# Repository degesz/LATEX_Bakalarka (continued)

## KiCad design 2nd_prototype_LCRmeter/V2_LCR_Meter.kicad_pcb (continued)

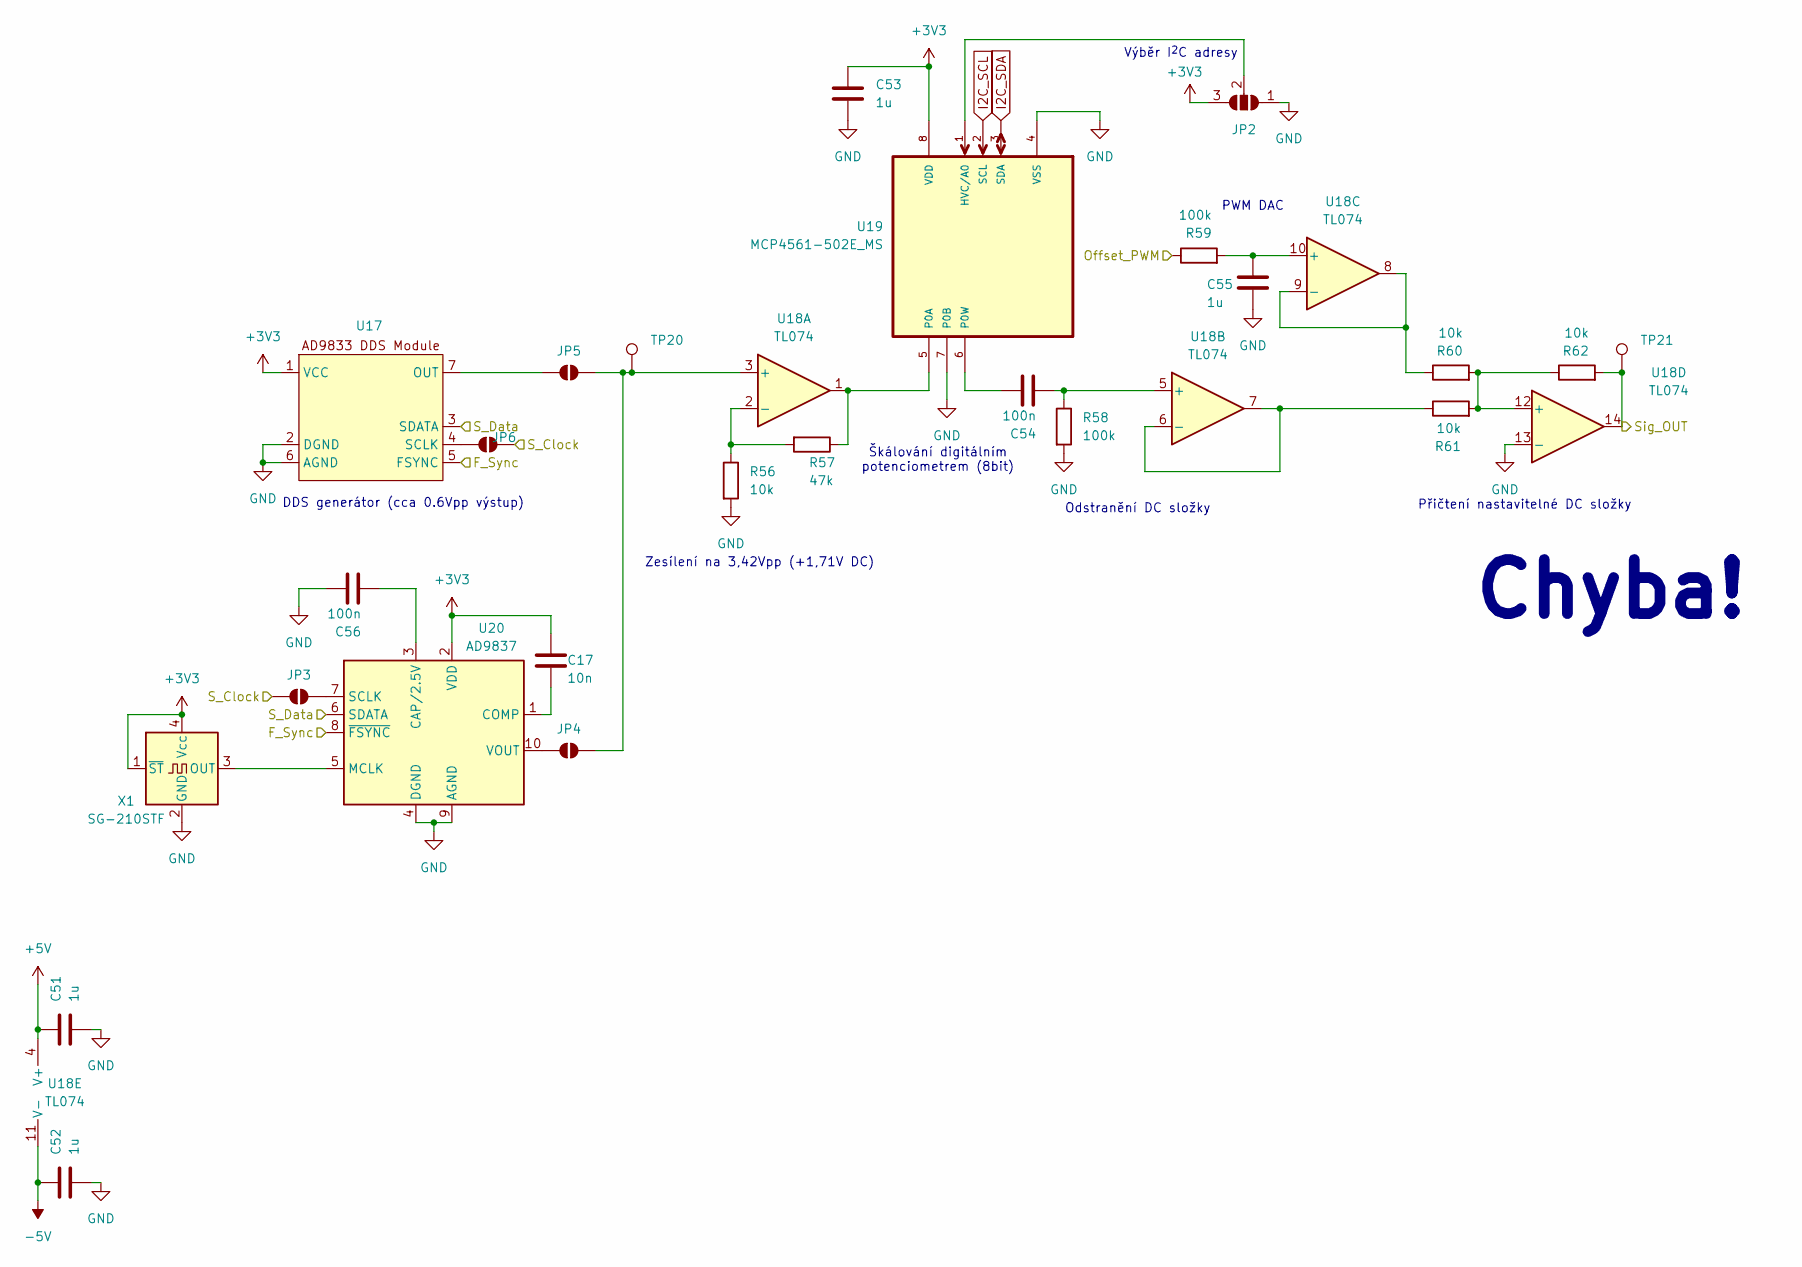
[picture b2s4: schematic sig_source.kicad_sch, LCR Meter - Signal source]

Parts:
C17: 10n; C_0603_1608Metric_Pad1.08x0.95mm_HandSolder
C51, C52, C53, C55: 1u; C_0603_1608Metric_Pad1.08x0.95mm_HandSolder
C54, C56: 100n; C_0603_1608Metric_Pad1.08x0.95mm_HandSolder
JP2: SolderJumper_3_Open; SolderJumper-3_P1.3mm_Open_RoundedPad1.0x1.5mm
JP3, JP4, JP5, JP6: SolderJumper_2_Open; SolderJumper-2_P1.3mm_Open_RoundedPad1.0x1.5mm
R56, R60, R61, R62: 10k; R_0603_1608Metric_Pad0.98x0.95mm_HandSolder
R57: 47k; R_0603_1608Metric_Pad0.98x0.95mm_HandSolder
R58, R59: 100k; R_0603_1608Metric_Pad0.98x0.95mm_HandSolder
TP20, TP21: TestPoint; Pin_D1.0mm_L10.0mm
U17: AD9833_Module
U18: TL074; TSSOP-14_4.4x5mm_P0.65mm
U19: MCP4561-502E_MS; MSOP-8_3x3mm_P0.65mm; MPN MCP4561-502E/MS
U20: AD9837; LFCSP-WD-10-1EP_3x3mm_P0.5mm_EP1.64x2.38mm
X1: SG-210STF; Oscillator_SMD_SeikoEpson_SG210-4Pin_2.5x2.0mm

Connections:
+3V3: C17.1, C53.2, JP2.3 (B), U17.1 (VCC), U19.8 (VDD), U20.2 (VDD), X1.1 (~ST), X1.4 (Vcc); also elsewhere on the board
+5V: C51.2, U18.4 (V+); also elsewhere on the board
-5V: C52.2, U18.11 (V-); also elsewhere on the board
/Analog frontend/Sig_IN: R62.2, TP21.1, U18.14; also elsewhere on the board
/Drive signal source/F_Sync: U17.5 (FSYNC), U20.8 (~FSYNC); also elsewhere on the board
/Drive signal source/Offset_PWM: R59.1; also elsewhere on the board
/Drive signal source/S_Clock: JP3.1 (A), JP6.2 (B); also elsewhere on the board
/Drive signal source/S_Data: U17.3 (SDATA), U20.6 (SDATA); also elsewhere on the board
GND: C51.1, C52.1, C53.1, C55.1, C56.2, JP2.1 (A), R56.2, R58.2, U17.2 (DGND), U17.6 (AGND), U18.13 (-), U19.4 (VSS), U19.7 (P0B), U20.4 (DGND), U20.9 (AGND), X1.2 (GND); also elsewhere on the board
I2C_SCL: U19.2 (SCL); also elsewhere on the board
I2C_SDA: U19.3 (SDA); also elsewhere on the board
unnamed: JP2.2 (C), U19.1 (HVC/A0)
unnamed: JP3.2 (B), U20.7 (SCLK)
unnamed: JP4.1 (A), U20.10 (VOUT)
unnamed: JP4.2 (B), JP5.2 (B), TP20.1, U18.3 (+)
unnamed: JP5.1 (A), U17.7 (OUT)
unnamed: JP6.1 (A), U17.4 (SCLK)
unnamed: R56.1, R57.2, U18.2 (-)
unnamed: C54.1, R58.1, U18.5 (+)
unnamed: R61.1, U18.6 (-), U18.7
unnamed: C55.2, R59.2, U18.10 (+)
unnamed: R60.1, U18.8, U18.9 (-)
unnamed: R60.2, R61.2, R62.1, U18.12 (+)
unnamed: R57.1, U18.1, U19.5 (P0A)
unnamed: C54.2, U19.6 (P0W)
unnamed: C56.1, U20.3 (CAP/2.5V)
unnamed: C17.2, U20.1 (COMP)
unnamed: U20.5 (MCLK), X1.3 (OUT)

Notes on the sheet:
Výběr I^{2}C adresy
Škálování digitálním potenciometrem (8bit)
Přičtení nastavitelné DC složky
Odstranění DC složky
Zesílení na 3,42Vpp (+1,71V DC)
DDS generátor (cca 0.6Vpp výstup)
Chyba!
PWM DAC

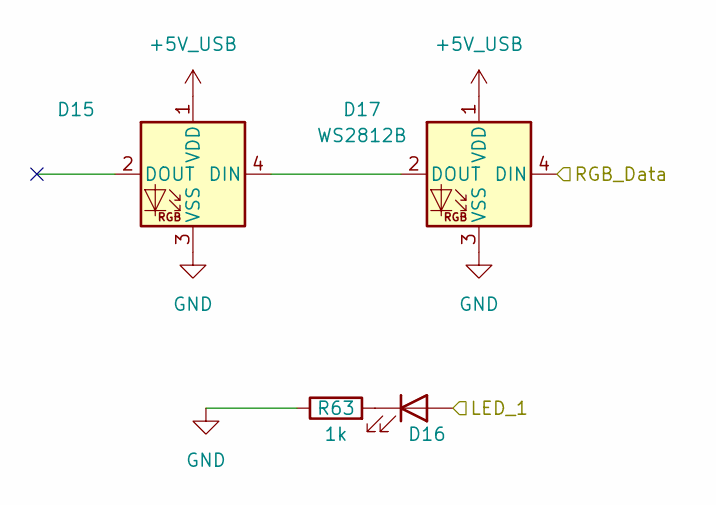
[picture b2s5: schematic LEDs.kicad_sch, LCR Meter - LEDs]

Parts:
D15, D17: WS2812B; LED_WS2812B_PLCC4_5.0x5.0mm_P3.2mm
D16: LED; LED_miniPLCC_2315
R63: 1k; R_0603_1608Metric_Pad0.98x0.95mm_HandSolder

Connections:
+5V_USB: D15.1 (VDD), D17.1 (VDD); also elsewhere on the board
/LEDs/LED_1: D16.2 (A); also elsewhere on the board
/LEDs/RGB_Data: D17.4 (DIN); also elsewhere on the board
GND: D15.3 (VSS), D17.3 (VSS), R63.1; also elsewhere on the board
unnamed: D15.4 (DIN), D17.2 (DOUT)
unnamed: D16.1 (K), R63.2

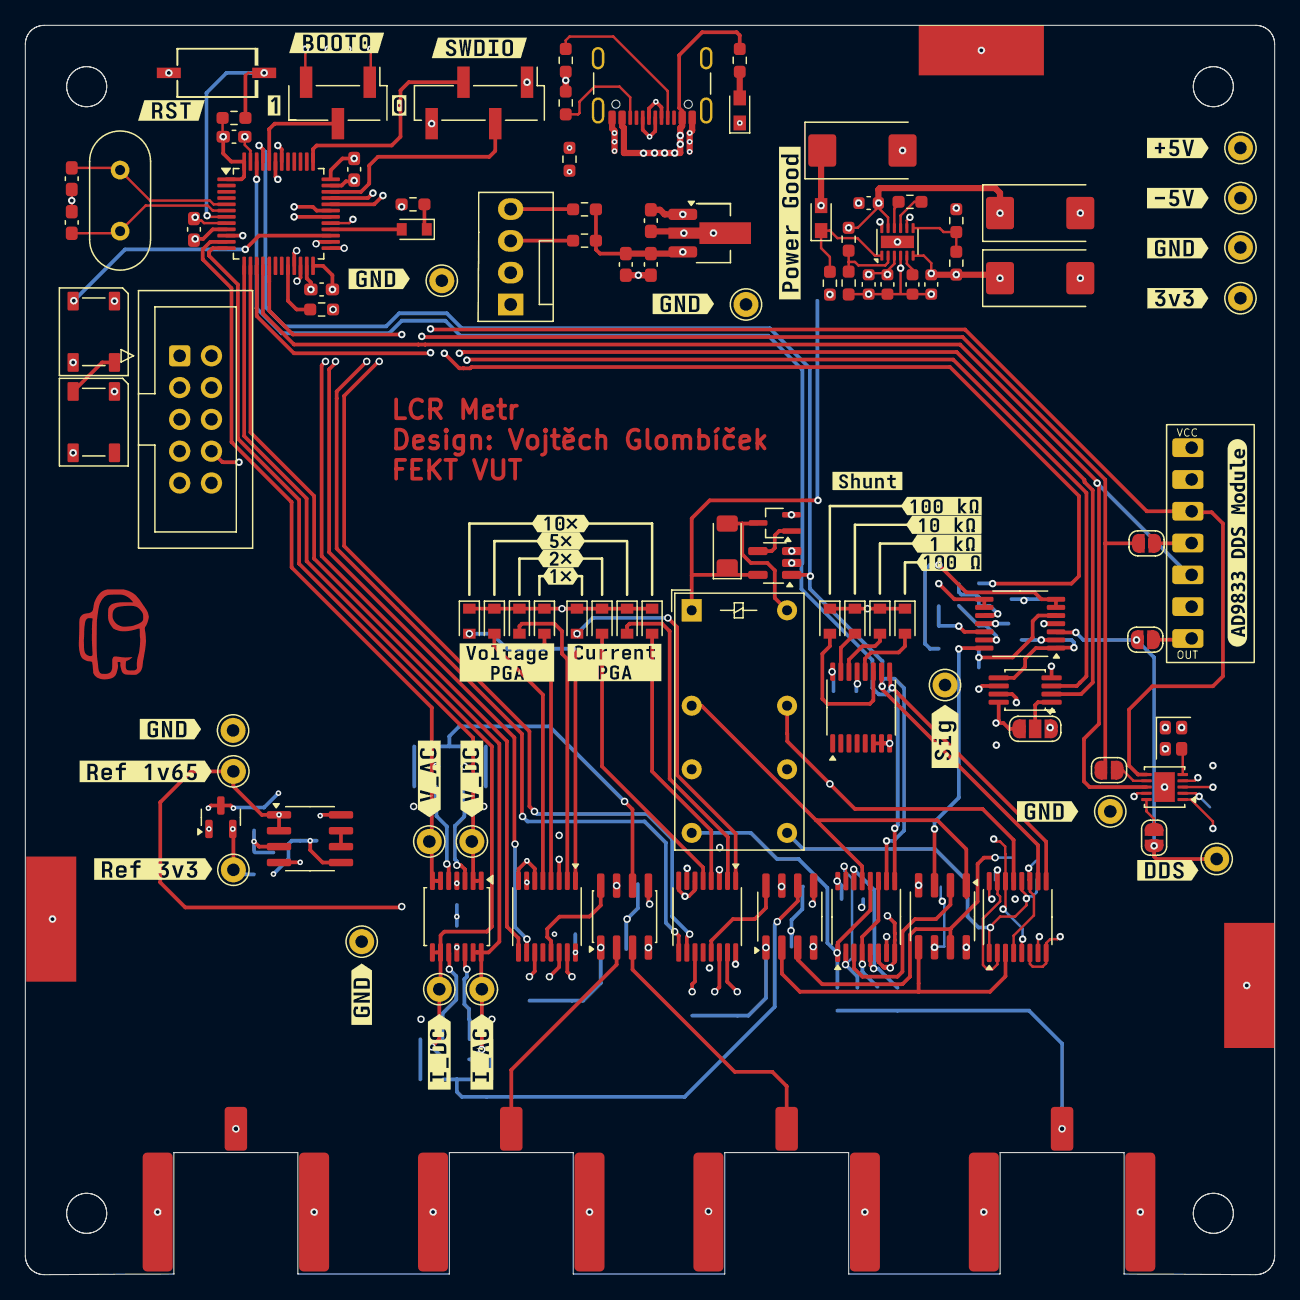
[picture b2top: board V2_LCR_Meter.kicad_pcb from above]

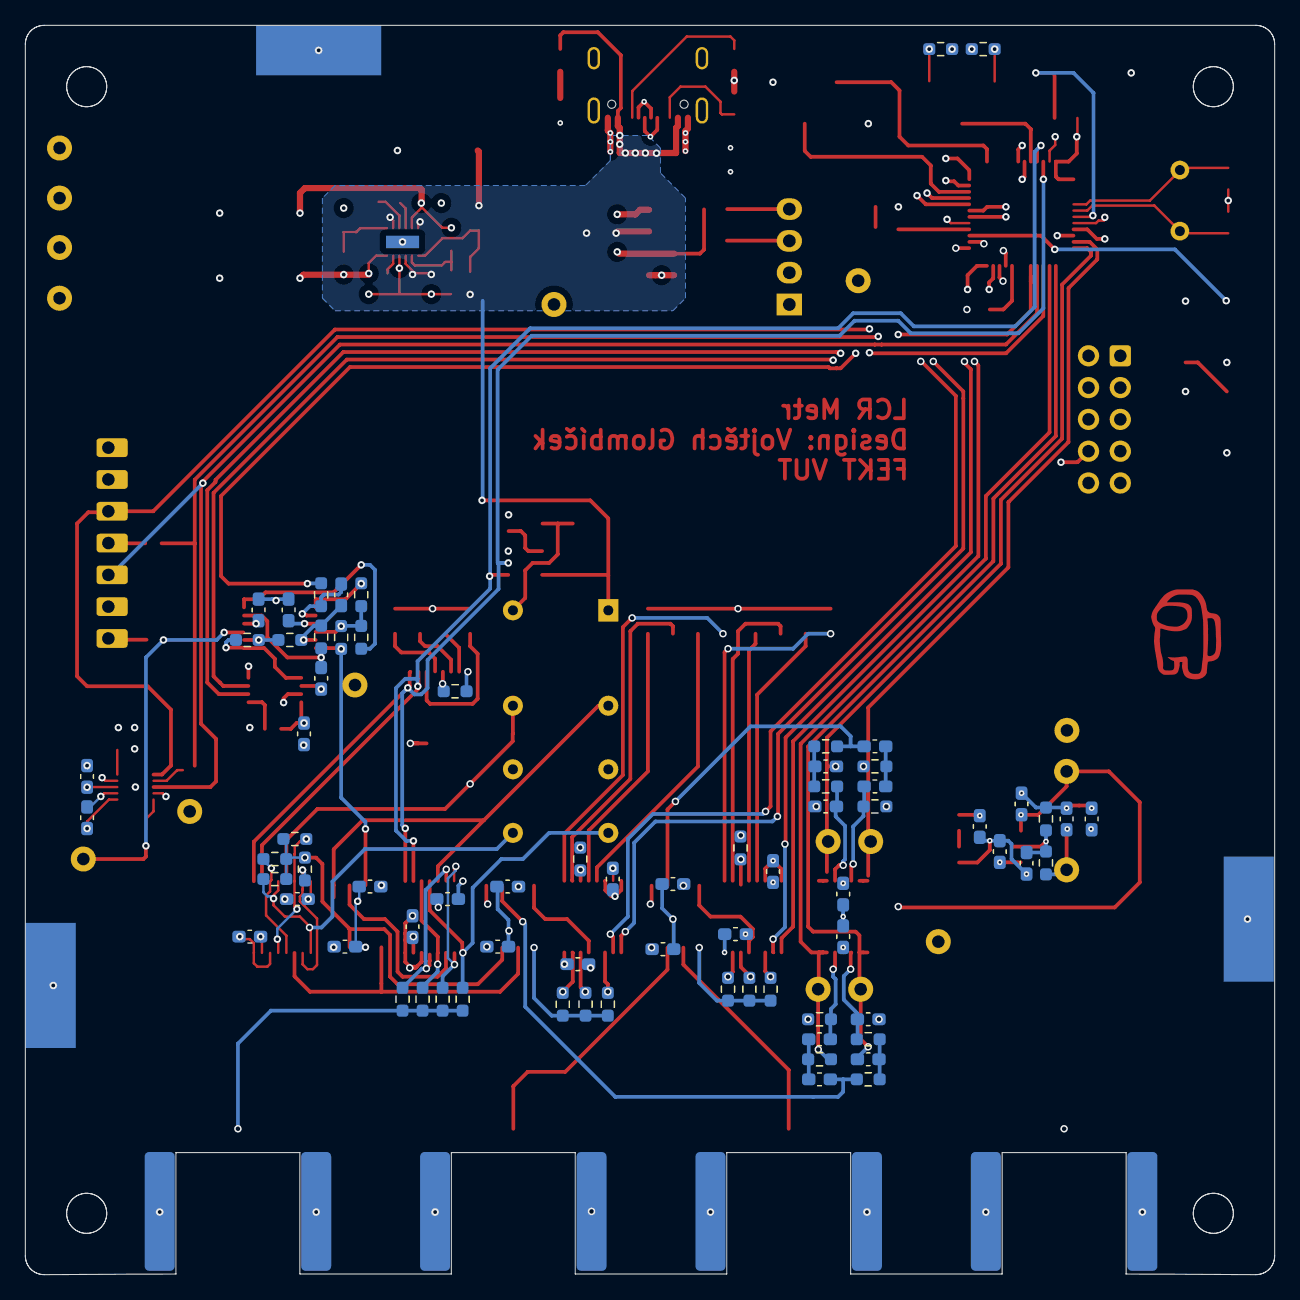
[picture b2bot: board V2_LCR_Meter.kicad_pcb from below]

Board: 6 copper layers, 99.8 x 99.8 mm, 212 parts (73 on the bottom side), 123 nets.

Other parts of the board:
kibuzzard-69A6FBA9: G***; kibuzzard-69A6FBA9
kibuzzard-69A6FBC7: G***; kibuzzard-69A6FBC7
kibuzzard-69A6FBD5: G***; kibuzzard-69A6FBD5
kibuzzard-69A6FBDC: G***; kibuzzard-69A6FBDC
kibuzzard-69A6FC6B: G***; kibuzzard-69A6FC6B
kibuzzard-69A6FC8C: G***; kibuzzard-69A6FC8C
kibuzzard-69A6FD3E: G***; kibuzzard-69A6FD3E
kibuzzard-69A6FD14: G***; kibuzzard-69A6FD14
kibuzzard-69A6FD47: G***; kibuzzard-69A6FD47
kibuzzard-69A6FD75: G***; kibuzzard-69A6FD75
kibuzzard-69A6FDE1: G***; kibuzzard-69A6FDE1
kibuzzard-69A0511F: G***; kibuzzard-69A0511F
kibuzzard-69A0516F: G***; kibuzzard-69A0516F
kibuzzard-69A0517C: G***; kibuzzard-69A0517C
kibuzzard-69B032D8: G***; kibuzzard-69B032D8
kibuzzard-69B032F6: G***; kibuzzard-69B032F6
kibuzzard-69B01019: G***; kibuzzard-69B01019
kibuzzard-69B01039: G***; kibuzzard-69B01039
kibuzzard-69B01057: G***; kibuzzard-69B01057
kibuzzard-69B03341: G***; kibuzzard-69B03341
kibuzzard-69B03368: G***; kibuzzard-69B03368
kibuzzard-69B03378: G***; kibuzzard-69B03378
kibuzzard-699D9FD2: G***; kibuzzard-699D9FD2
kibuzzard-699DA05C: G***; kibuzzard-699DA05C
kibuzzard-699DA06A, kibuzzard-699DA06A#2, kibuzzard-699DA06A#3, kibuzzard-699DA06A#4, kibuzzard-699DA06A#5, kibuzzard-699DA06A#6: G***; kibuzzard-699DA06A
kibuzzard-699DA06F: G***; kibuzzard-699DA06F
kibuzzard-699DA048: G***; kibuzzard-699DA048
kibuzzard-699DB946: G***; kibuzzard-699DB946
kibuzzard-699DC026: G***; kibuzzard-699DC026

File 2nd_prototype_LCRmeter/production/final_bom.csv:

Designator,Footprint,Quantity,Value,LCSC Part #
"C1, C2",0603,2,20p,
"C10, C14, C19, C20, C21, C22, C23, C24, C25, C26, C27, C3, C31, C35, C36, C37, C38, C39, C4, C40, C41, C42, C5, C51, C52, C53, C55, C6",0603,28,1u,
"C11, C12, C28, C32, C33, C34, C43, C44, C45, C46, C47, C48, C49, C50, C54, C56",0603,16,100n,
"C13, C15, C16, C8, C9",0603,5,4.7u,
C17,0603,1,10n,
"C18, C29, C7",CP_EIA-7343-30_AVX-N_HandSolder,3,470u,
"D1, D18",LED_miniPLCC_2315_Handsoldering,2,LED,
"D10, D11, D12, D13, D16, D2, D3, D4, D5, D6, D7, D8, D9",LED_miniPLCC_2315,13,LED,
D14,D_MiniMELF,1,D_Schottky,
"D15, D17",LED_WS2812B_PLCC4_5.0x5.0mm_P3.2mm,2,WS2812B,
J1,PinHeader_1x04_P2.54mm_Vertical_SMD_Pin1Left,1,ST-Link,
J2,FanPinHeader_1x04_P2.54mm_Vertical,1,Display OLED,
J3,IDC-Header_2x05_P2.54mm_Vertical,1,IDC 2x5,
J4,USB_C_Receptacle_GCT_USB4105-xx-A_16P_TopMnt_Horizontal,1,USB_C_Receptacle_USB2.0_16P,
"J6, J7, J8, J9",BNC_Gold,4,Conn_Coaxial,
K1,Relay_DPDT_Finder_30.22,1,Relay_DPDT,
Q1,SOT-323_SC-70_Handsoldering,1,NX3008NBK,
"R1, R22, R3, R35, R4, R54, R55, R56, R60, R61, R62, R64",0603,12,10k,
"R10, R11, R7",0603,3,1k5,
"R12, R2, R5, R9",0603,4,4k7,
"R13, R21, R34, R37, R38, R6, R63, R8",0603,8,1k,
"R14, R17, R18, R19, R23, R24, R36, R39, R41, R42, R43, R44, R45, R58, R59",0603,15,100k,
"R15, R40",0603,2,25k,
R16,0603,1,11k,
"R20, R33",0603,2,100R,
R57,0603,1,47k,
"R65, R66",0603,2,5k1,
SW1,SW-SMD_L6.1-W3.7-LS7.9,1,SW_SPST,
"TP1, TP10, TP11, TP12, TP13, TP14, TP15, TP16, TP17, TP18, TP19, TP2, TP20, TP21, TP5, TP6, TP7",Pin_D1.0mm_L10.0mm,17,TestPoint,
U1,LQFP-48_7x7mm_P0.5mm,1,STM32F103C8Tx,
U10,SOIC-8_3.9x4.9mm_P1.27mm,1,TL072,
"U11, U13, U14, U5, U8",TSSOP-16_4.4x5mm_P0.65mm,5,CD74HC4052,
"U12, U6",SOIC-8_3.9x4.9mm_P1.27mm,2,INA823,
U15,SOT-23,1,REF3033,
U16,SOT-23-5_HandSoldering,1,74LVC1G02,
U17,AD9833_Module,1,~,
"U18, U7",TSSOP-14_4.4x5mm_P0.65mm,2,TL074,
U19,MSOP-8_3x3mm_P0.65mm,1,MCP4561-502E_MS,MCP4561-502E/MS
U2,WSON-12-1EP_3x2mm_P0.5mm_EP1x2.65_ThermalVias,1,LM27762,
U20,LFCSP-WD-10-1EP_3x3mm_P0.5mm_EP1.64x2.38mm,1,AD9837,
U3,SOT-89-3_Handsoldering,1,HT75xx-1-SOT89,
U4,SOIC-8_3.9x4.9mm_P1.27mm,1,OPA2192,
X1,Oscillator_SMD_SeikoEpson_SG210-4Pin_2.5x2.0mm,1,SG-210STF,
Y1,Crystal_HC49-U_Vertical,1,8MHz,

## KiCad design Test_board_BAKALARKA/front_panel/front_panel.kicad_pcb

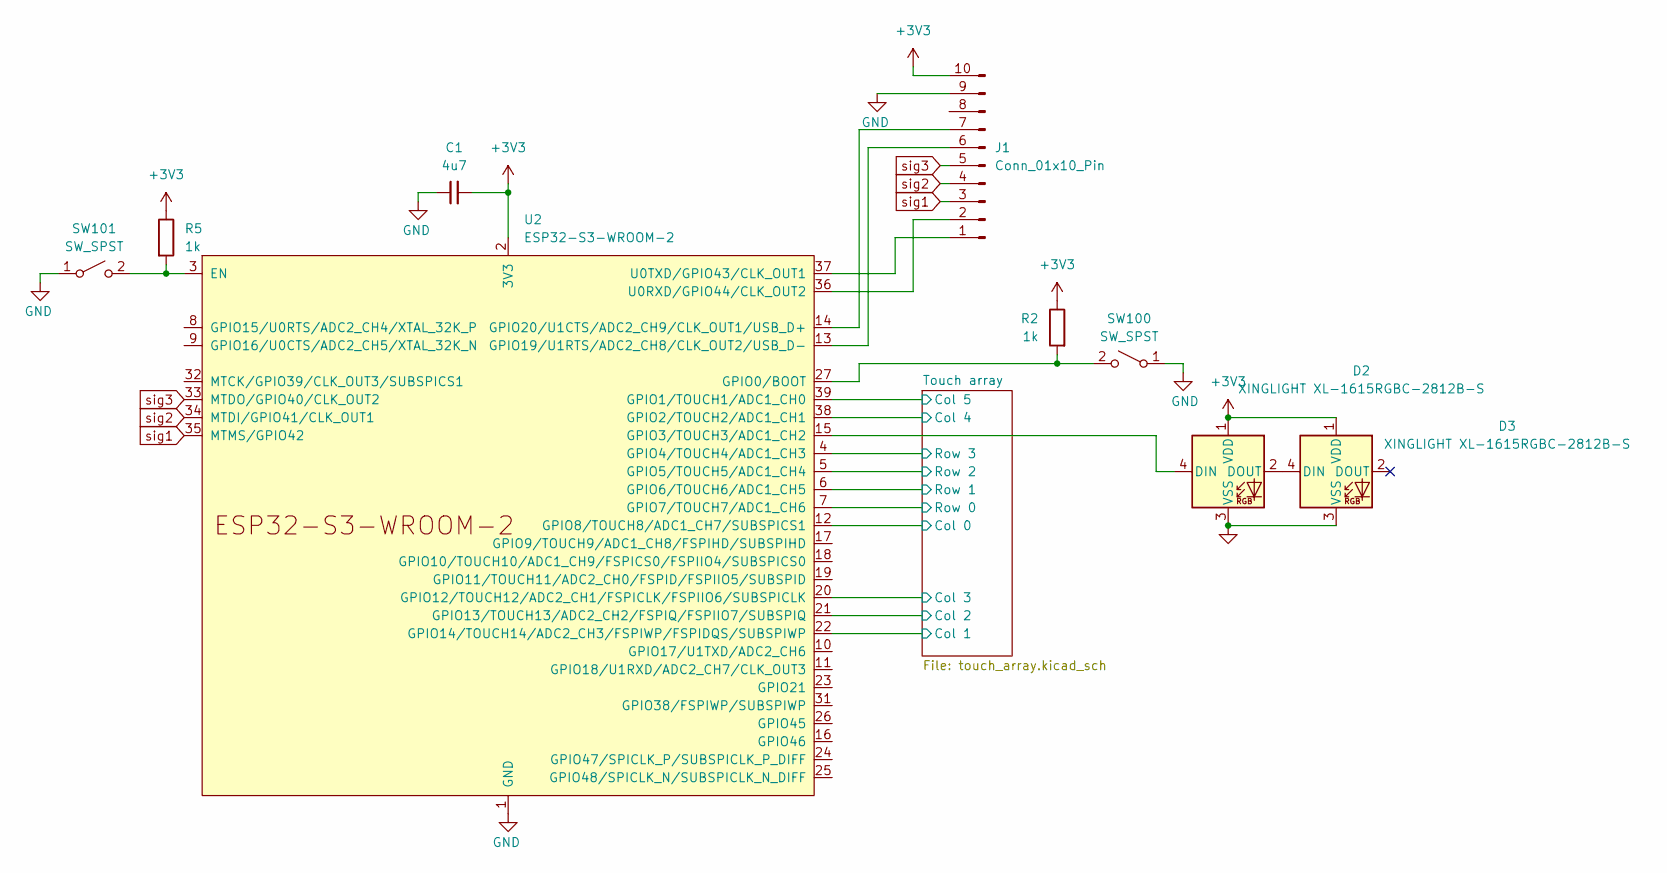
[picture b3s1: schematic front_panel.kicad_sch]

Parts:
C1: 4u7; C_0805_2012Metric_Pad1.18x1.45mm_HandSolder
D2: XINGLIGHT XL-1615RGBC-2812B-S
D3: XINGLIGHT XL-1615RGBC-2812B-S; Flipped_XINGLIGHT XL-1615RGBC-2812B-S_1
J1: Conn_01x10_Pin; FFC_FPC_10pin_connector
R2, R5: 1k; R_0603_1608Metric_Pad0.98x0.95mm_HandSolder
SW100, SW101: SW_SPST; SW_SPST_CK_RS282G05A3
U2: ESP32-S3-WROOM-2

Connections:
+3V3: C1.2, D2.1 (VDD), D3.1 (VDD), J1.10, R2.1, R5.1, U2.2 (3V3)
/Touch array/Col 0: U2.12 (GPIO8/TOUCH8/ADC1_CH7/SUBSPICS1); also elsewhere on the board
/Touch array/Col 1: U2.22 (GPIO14/TOUCH14/ADC2_CH3/FSPIWP/FSPIDQS/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); also elsewhere on the board
/Touch array/Col 2: U2.21 (GPIO13/TOUCH13/ADC2_CH2/FSPIQ/FSPIIO7/S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); also elsewhere on the board
/Touch array/Col 3: U2.20 (GPIO12/TOUCH12/ADC2_CH1/FSPICLK/FSPIIO6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); also elsewhere on the board
/Touch array/Col 4: U2.38 (GPIO2/TOUCH2/ADC1_CH1); also elsewhere on the board
/Touch array/Col 5: U2.39 (GPIO1/TOUCH1/ADC1_CH0); also elsewhere on the board
/Touch array/Row 0: U2.7 (GPIO7/TOUCH7/ADC1_CH6); also elsewhere on the board
/Touch array/Row 1: U2.6 (GPIO6/TOUCH6/ADC1_CH5); also elsewhere on the board
/Touch array/Row 2: U2.5 (GPIO5/TOUCH5/ADC1_CH4); also elsewhere on the board
/Touch array/Row 3: U2.4 (GPIO4/TOUCH4/ADC1_CH3); also elsewhere on the board
GND: C1.1, D2.3 (VSS), D3.3 (VSS), J1.9, SW100.1 (A), SW101.1 (A), U2.1 (GND), U2.40 (GND), U2.41 (GND)
unnamed: D2.4 (DIN), U2.15 (GPIO3/TOUCH3/ADC1_CH2)
unnamed: D2.2 (DOUT), D3.4 (DIN)
unnamed: J1.1, U2.37 (U0TXD/GPIO43/CLK_OUT1)
unnamed: J1.2, U2.36 (U0RXD/GPIO44/CLK_OUT2)
unnamed: J1.6, U2.13 (GPIO19/U1RTS/ADC2_CH8/CLK_OUT2/USB_D-)
unnamed: J1.7, U2.14 (GPIO20/U1CTS/ADC2_CH9/CLK_OUT1/USB_D+)
unnamed: R2.2, SW100.2 (B), U2.27 (GPIO0/BOOT)
unnamed: R5.2, SW101.2 (B), U2.3 (EN)
sig1: J1.3, U2.35 (MTMS/GPIO42)
sig2: J1.4, U2.34 (MTDI/GPIO41/CLK_OUT1)
sig3: J1.5, U2.33 (MTDO/GPIO40/CLK_OUT2)

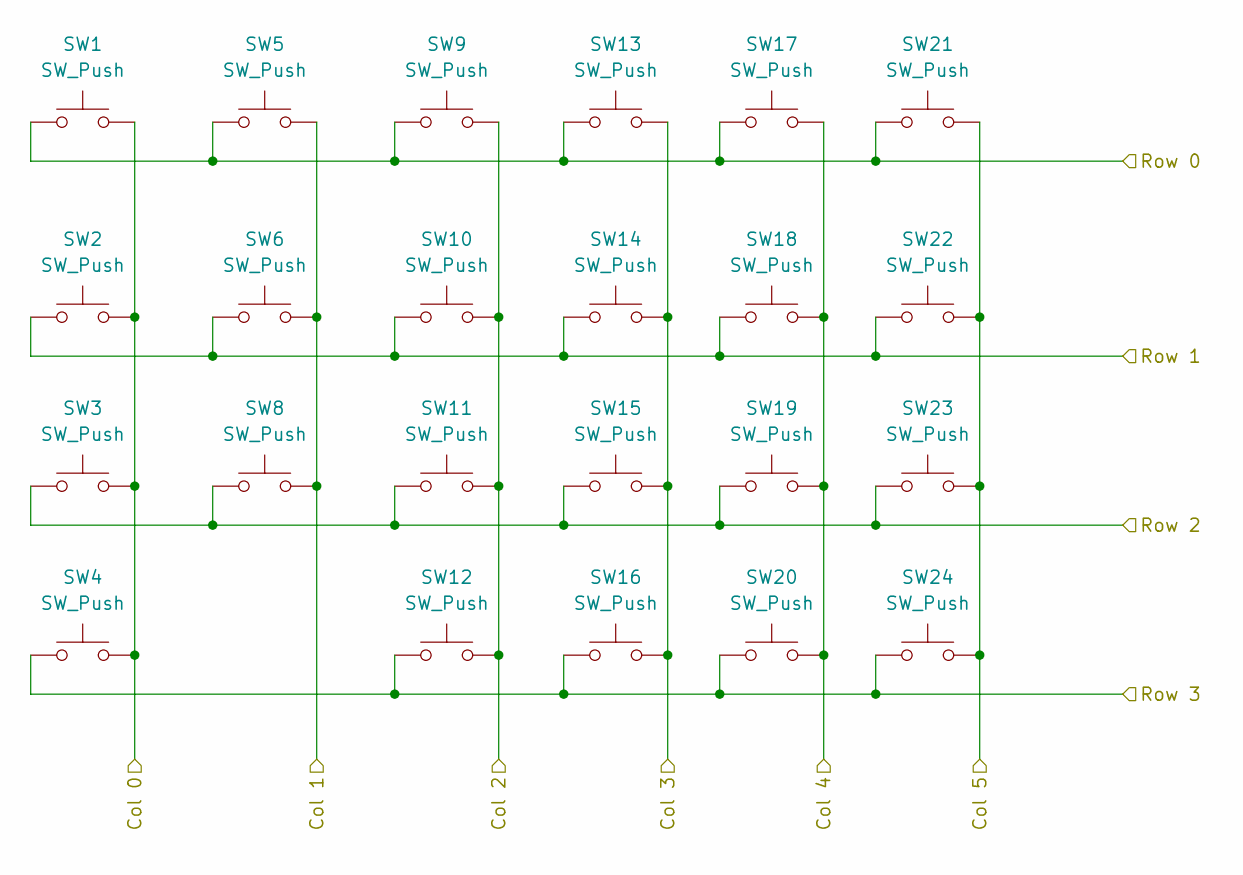
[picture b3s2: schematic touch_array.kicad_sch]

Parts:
SW1, SW2, SW3, SW4, SW9, SW10, SW11, SW12, SW13, SW14, SW15, SW16, SW17, SW18, SW19, SW20, SW21, SW22, SW23, SW24: SW_Push; Cap_Touch_Pad
SW5, SW8: SW_Push; cap_touch_triangle
SW6: SW_Push; Cap_Touch_Pad_big

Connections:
/Touch array/Col 0: SW1.2, SW2.2, SW3.2, SW4.2; also elsewhere on the board
/Touch array/Col 1: SW5.2, SW6.2, SW8.2; also elsewhere on the board
/Touch array/Col 2: SW9.2, SW10.2, SW11.2, SW12.2; also elsewhere on the board
/Touch array/Col 3: SW13.2, SW14.2, SW15.2, SW16.2; also elsewhere on the board
/Touch array/Col 4: SW17.2, SW18.2, SW19.2, SW20.2; also elsewhere on the board
/Touch array/Col 5: SW21.2, SW22.2, SW23.2, SW24.2; also elsewhere on the board
/Touch array/Row 0: SW1.1, SW5.1, SW9.1, SW13.1, SW17.1, SW21.1; also elsewhere on the board
/Touch array/Row 1: SW2.1, SW6.1, SW10.1, SW14.1, SW18.1, SW22.1; also elsewhere on the board
/Touch array/Row 2: SW3.1, SW8.1, SW11.1, SW15.1, SW19.1, SW23.1; also elsewhere on the board
/Touch array/Row 3: SW4.1, SW12.1, SW16.1, SW20.1, SW24.1; also elsewhere on the board

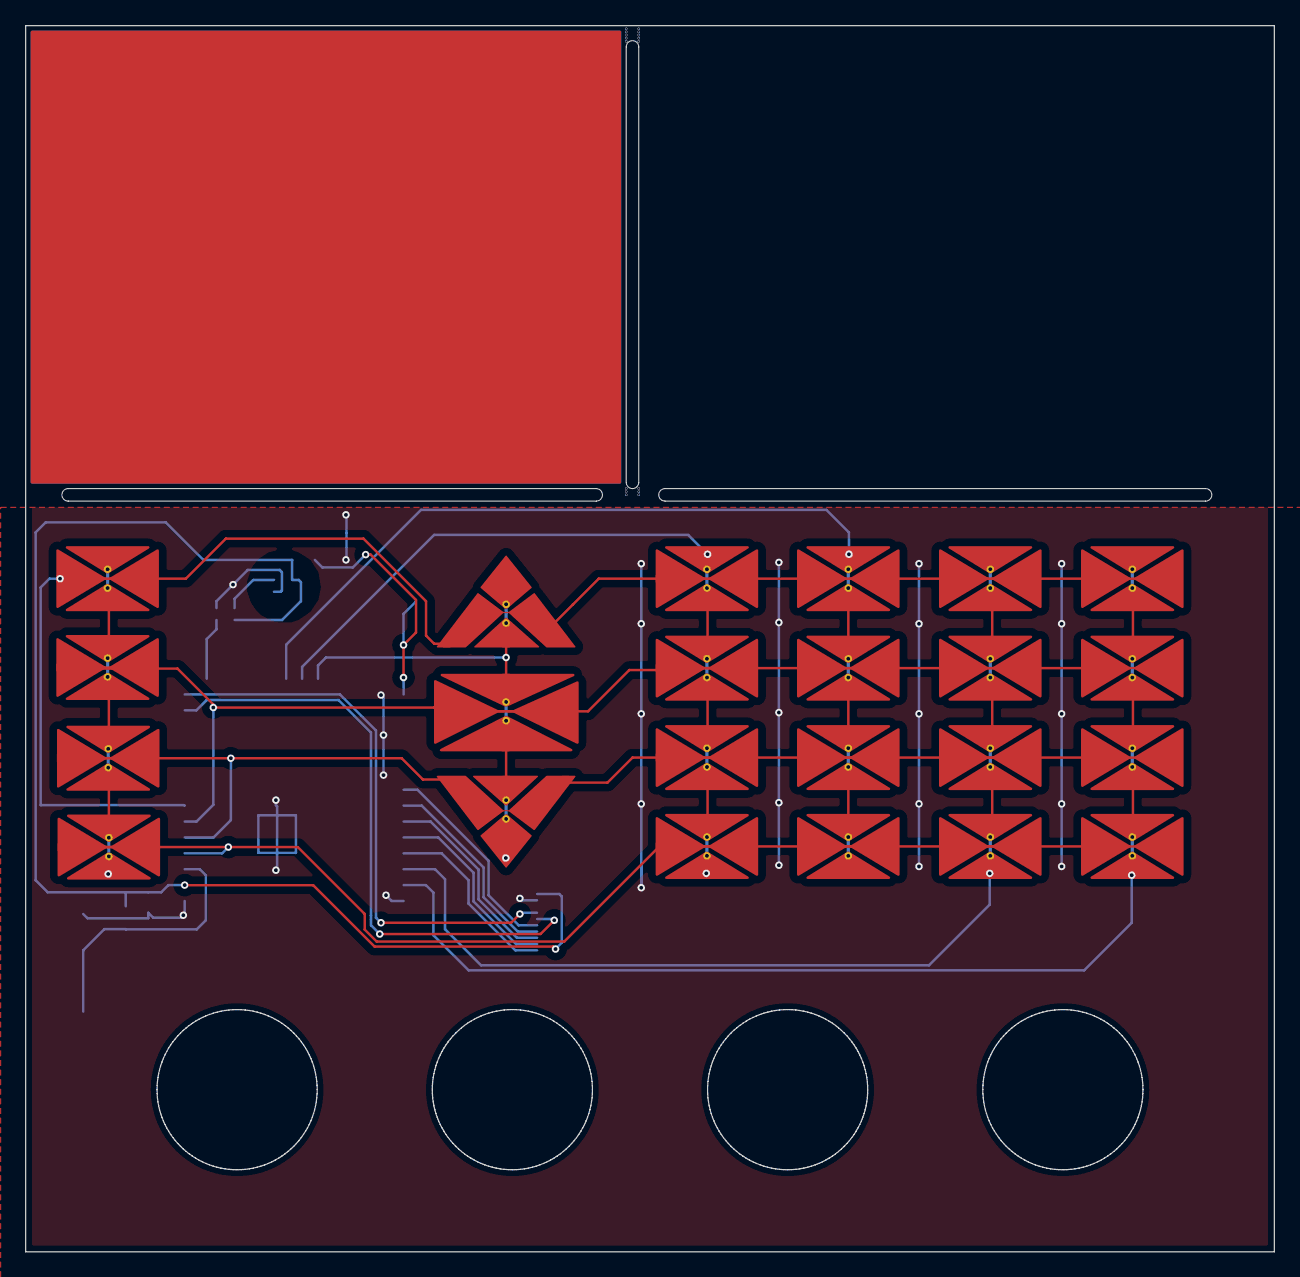
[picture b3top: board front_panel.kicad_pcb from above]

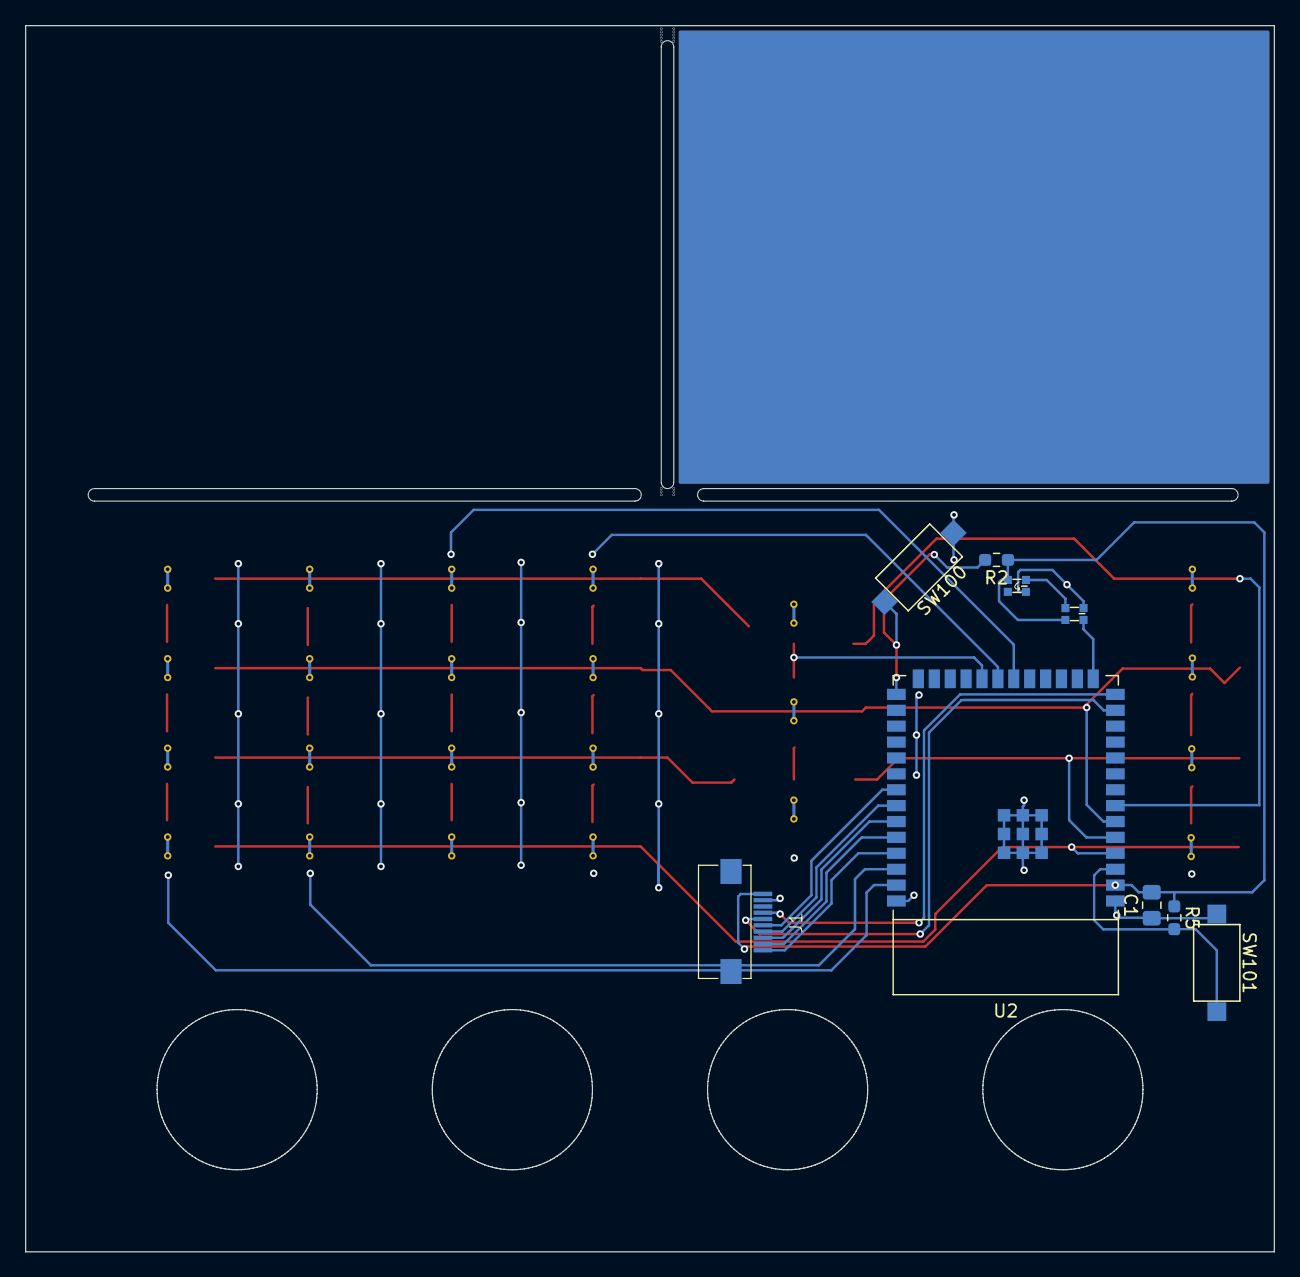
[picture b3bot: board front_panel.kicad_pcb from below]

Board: 2 copper layers, 99.8 x 98.0 mm, 32 parts (9 on the bottom side), 23 nets.

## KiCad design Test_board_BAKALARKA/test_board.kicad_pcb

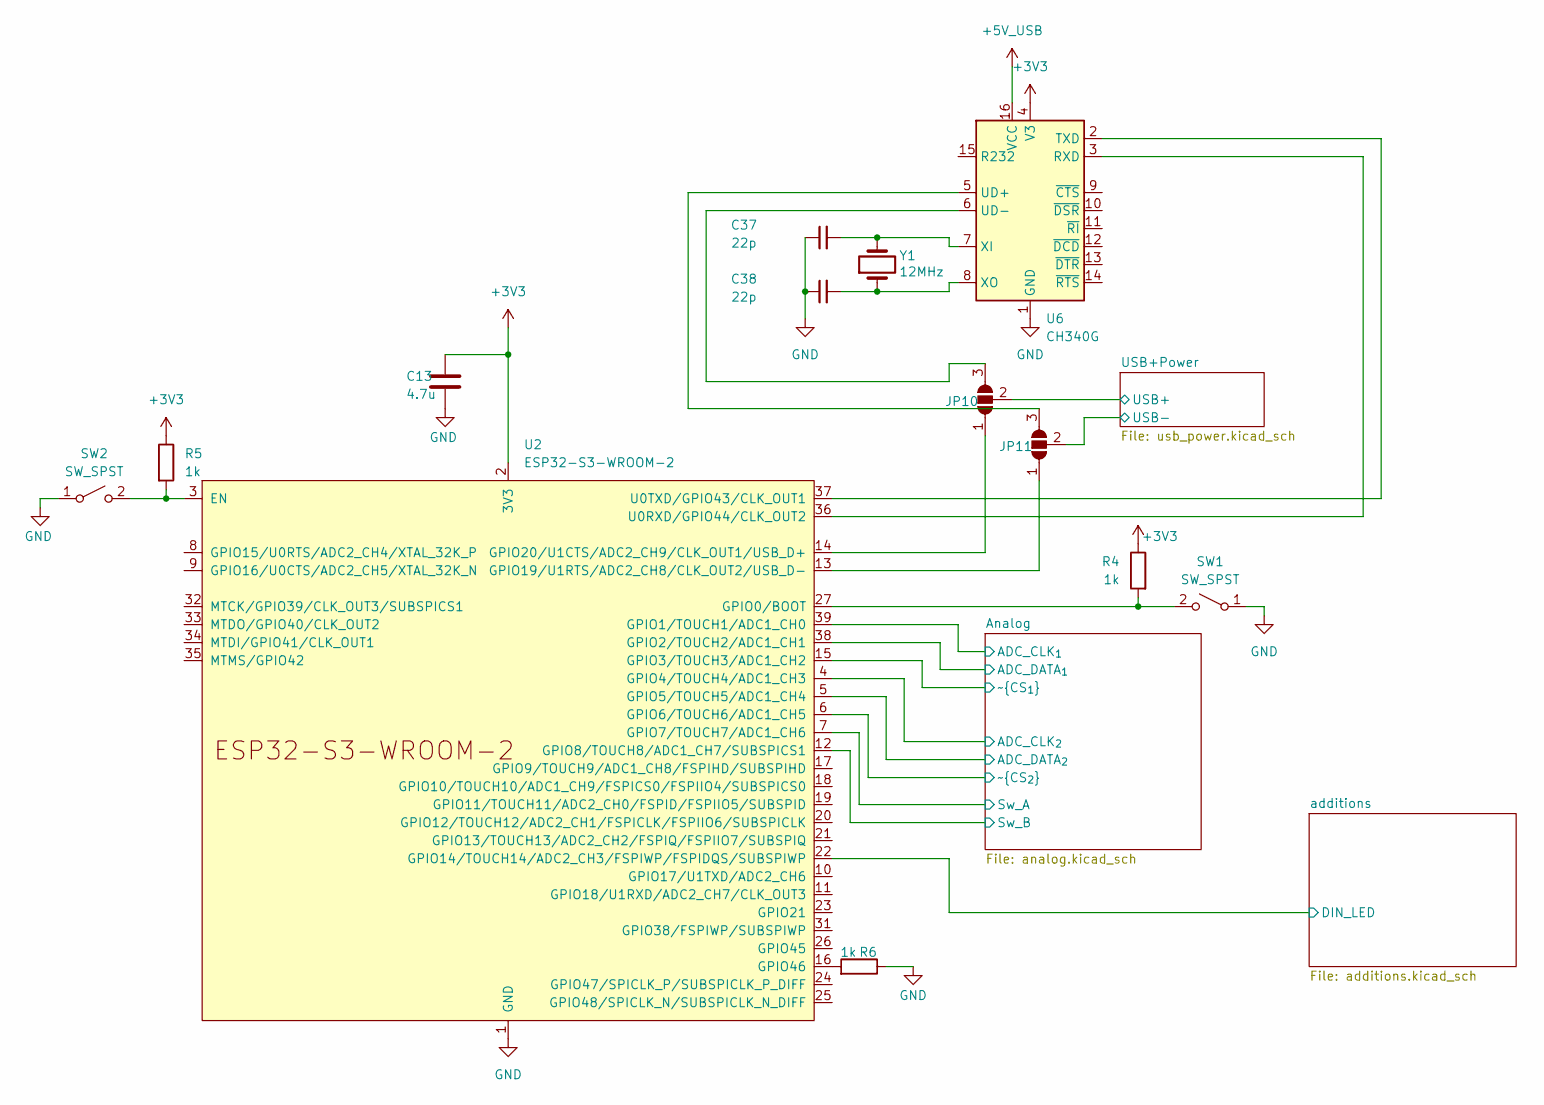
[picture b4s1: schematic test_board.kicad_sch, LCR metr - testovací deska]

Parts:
C13: 4.7u; C_0805_2012Metric_Pad1.18x1.45mm_HandSolder
C37, C38: 22p; C_0603_1608Metric_Pad1.08x0.95mm_HandSolder
JP10, JP11: SolderJumper_3_Open; SolderJumper-3_P1.3mm_Open_RoundedPad1.0x1.5mm
R4, R5, R6: 1k; R_0603_1608Metric_Pad0.98x0.95mm_HandSolder
SW1, SW2: SW_SPST; SW_SPST_CK_RS282G05A3
U2: ESP32-S3-WROOM-2
U6: CH340G; SOIC-16_3.9x9.9mm_P1.27mm
Y1: 12MHz; Crystal_SMD_HC49-SD_HandSoldering

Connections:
+3V3: C13.1, R4.1, R5.1, U2.2 (3V3), U6.4 (V3); also elsewhere on the board
+5V_USB: U6.16 (VCC); also elsewhere on the board
/Analog/ADC_CLK_{1}: U2.39 (GPIO1/TOUCH1/ADC1_CH0); also elsewhere on the board
/Analog/ADC_CLK_{2}: U2.4 (GPIO4/TOUCH4/ADC1_CH3); also elsewhere on the board
/Analog/ADC_DATA_{1}: U2.38 (GPIO2/TOUCH2/ADC1_CH1); also elsewhere on the board
/Analog/ADC_DATA_{2}: U2.5 (GPIO5/TOUCH5/ADC1_CH4); also elsewhere on the board
/Analog/Sw_A: U2.7 (GPIO7/TOUCH7/ADC1_CH6); also elsewhere on the board
/Analog/Sw_B: U2.12 (GPIO8/TOUCH8/ADC1_CH7/SUBSPICS1); also elsewhere on the board
/Analog/~CS_{1}: U2.15 (GPIO3/TOUCH3/ADC1_CH2); also elsewhere on the board
/Analog/~CS_{2}: U2.6 (GPIO6/TOUCH6/ADC1_CH5); also elsewhere on the board
/USB+Power/USB+: JP10.2 (C); also elsewhere on the board
/USB+Power/USB-: JP11.2 (C); also elsewhere on the board
/additions/DIN_LED: U2.22 (GPIO14/TOUCH14/ADC2_CH3/FSPIWP/FSPIDQS/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); also elsewhere on the board
GND: C13.2, C37.1, C38.1, R6.1, SW1.1 (A), SW2.1 (A), U2.1 (GND), U2.40 (GND), U2.41 (GND), U6.1 (GND); also elsewhere on the board
unnamed: JP10.1 (A), U2.14 (GPIO20/U1CTS/ADC2_CH9/CLK_OUT1/USB_D+)
unnamed: JP10.3 (B), U6.6 (UD-)
unnamed: JP11.1 (A), U2.13 (GPIO19/U1RTS/ADC2_CH8/CLK_OUT2/USB_D-)
unnamed: JP11.3 (B), U6.5 (UD+)
unnamed: R4.2, SW1.2 (B), U2.27 (GPIO0/BOOT)
unnamed: R5.2, SW2.2 (B), U2.3 (EN)
unnamed: R6.2, U2.16 (GPIO46)
unnamed: U2.36 (U0RXD/GPIO44/CLK_OUT2), U6.3 (RXD)
unnamed: U2.37 (U0TXD/GPIO43/CLK_OUT1), U6.2 (TXD)
unnamed: C37.2, U6.7 (XI), Y1.2
unnamed: C38.2, U6.8 (XO), Y1.1

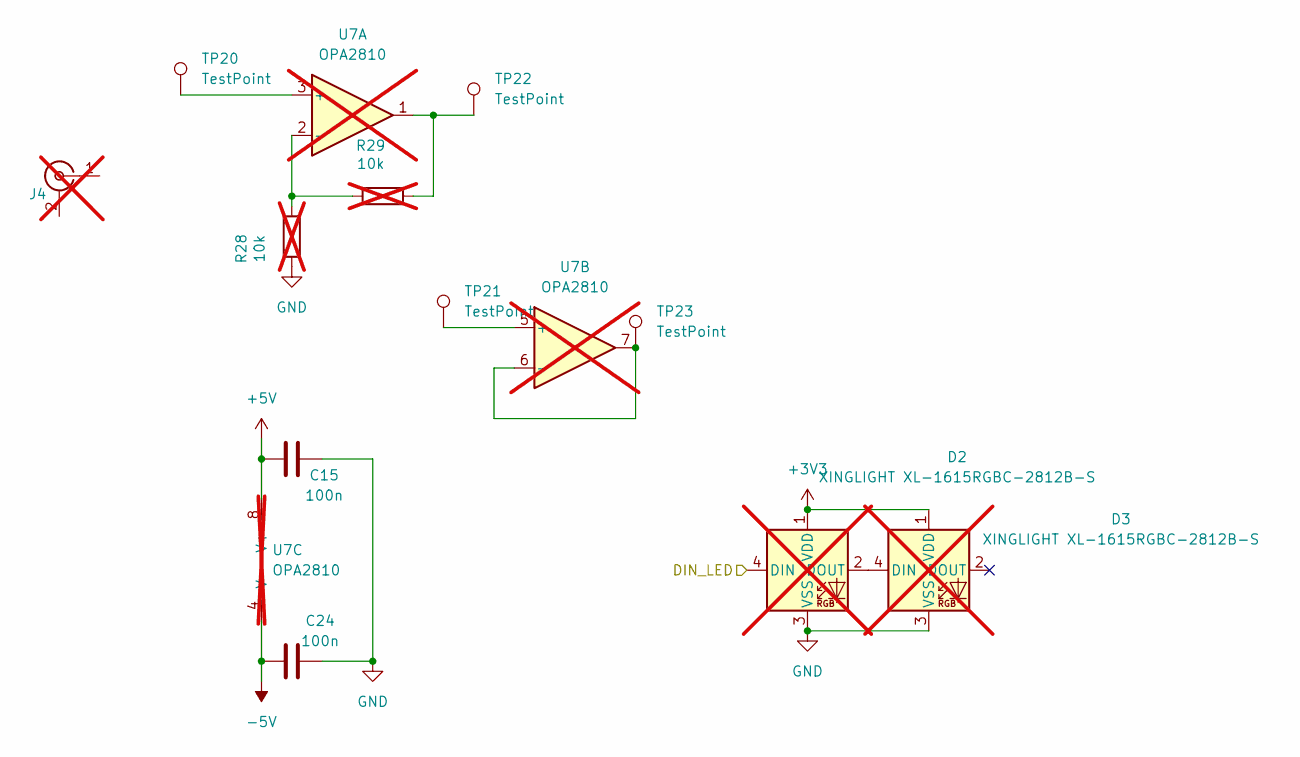
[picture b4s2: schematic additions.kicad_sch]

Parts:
C15, C24: 100n; C_0603_1608Metric_Pad1.08x0.95mm_HandSolder
D2, D3: XINGLIGHT XL-1615RGBC-2812B-S; not fitted
J4: Conn_Coaxial; BNC_Gold; not fitted
R28, R29: 10k; R_0603_1608Metric_Pad0.98x0.95mm_HandSolder; not fitted
TP20, TP21, TP22, TP23: TestPoint; Pin_D1.0mm_L10.0mm
U7: OPA2810; SOIC-8_3.9x4.9mm_P1.27mm; not fitted

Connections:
+3V3: D2.1 (VDD), D3.1 (VDD); also elsewhere on the board
+5V: C15.2, U7.8 (V+); also elsewhere on the board
-5V: C24.2, U7.4 (V-); also elsewhere on the board
/additions/DIN_LED: D2.4 (DIN); also elsewhere on the board
GND: C15.1, C24.1, D2.3 (VSS), D3.3 (VSS), R28.1; also elsewhere on the board
unnamed: D2.2 (DOUT), D3.4 (DIN)
unnamed: R29.2, TP22.1, U7.1
unnamed: TP20.1, U7.3 (+)
unnamed: R28.2, R29.1, U7.2 (-)
unnamed: TP21.1, U7.5 (+)
unnamed: TP23.1, U7.6 (-), U7.7
